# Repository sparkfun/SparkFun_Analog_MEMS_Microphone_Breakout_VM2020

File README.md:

SparkFun Analog MEMS Microphone Breakout - VM2020
========================================

[*SparkFun Analog MEMS Microphone Breakout VM2020 [BOB-21537]*](https://www.sparkfun.com/products/21537)

The SparkFun Analog MEMS Microphone Breakout makes it easy to work with the Vesper VM2020 analog microphone. The VM2020 is an ultra-high Acoustic Overload Point (AOP), high dynamic range, differential analog output piezoelectric MEMS microphone. What separates this from other analog MEMS microphones is that it was designed to be used in loud environments. Additionally, this microphone consists of a piezoelectric sensor and circuitry to buffer and amplify the output. It has an acoustic overload point of 152dB SPL for audio capture in loud environments.

Also note, this low-profile microphone has its port on the bottom side, so the microphone can be mounted flush to the outer surface of your enclosure. This microphone is omnidirectional, which means it does a good job of picking up sound sources from all directions.

Most microphone breakouts in SparkFun's catalog have an OpAmp which amplifies the signal and has a single-ended output. This microphone breakout is differential and does not have an OpAmp. To connect to the differential output with an Arduino, you will need to amplify the signal to a usable level and ADC with differential inputs. We recommend using the SparkFun WM8960 Audio Codec Breakout with a built-in programmable gain amplifier and ADC.

This board is great for applications that require you to measure volume in a loud environment, capture audio when the microphone is next to a speaker, fast Fourier transform analysis of sound at concerts, make your own electronic hearing protection, or create an adaptive filter for your smart speaker. Add the SparkFun VM2020 Analog MEMS Microphone Breakout to your next project!

Repository Contents
-------------------

* **/Documentation** - Data sheets, additional product information
* **/Hardware** - Eagle design files (.brd, .sch)
* **/Hardware/Production** - Production panel files (.brd)

Documentation
--------------
* **[Library](https://github.com/sparkfun/SparkFun_WM8960_Arduino_Library)** - Arduino library for the Stereo Audio Codec Breakout - WM8960 that has an example using a differential microphone (e.g. VM2020).
* **[Fritzing Part](https://github.com/sparkfun/Fritzing_Parts/blob/main/products/21537_sfe_analog_MEMS_microphone_VM2020_differential.fzpz)** - Fritzing diagrams for SparkFun products.
* **[Hookup Guide](https://learn.sparkfun.com/tutorials/2913)** - Basic hookup guide for the SparkFun MEMS microphone breakout.

Product Versions
---------------
* **[BOB-21537](https://www.sparkfun.com/products/21537)** - SparkFun Analog MEMS Microphone Breakout - VM2020

License Information
-------------------

This product is _**open source**_! 

Please review the LICENSE.md file for license information. 

If you have any questions or concerns on licensing, please contact technical support on our [SparkFun forums](https://forum.sparkfun.com/viewforum.php?f=152).

Distributed as-is; no warranty is given.

- Your friends at SparkFun.

_<COLLABORATION CREDIT>_

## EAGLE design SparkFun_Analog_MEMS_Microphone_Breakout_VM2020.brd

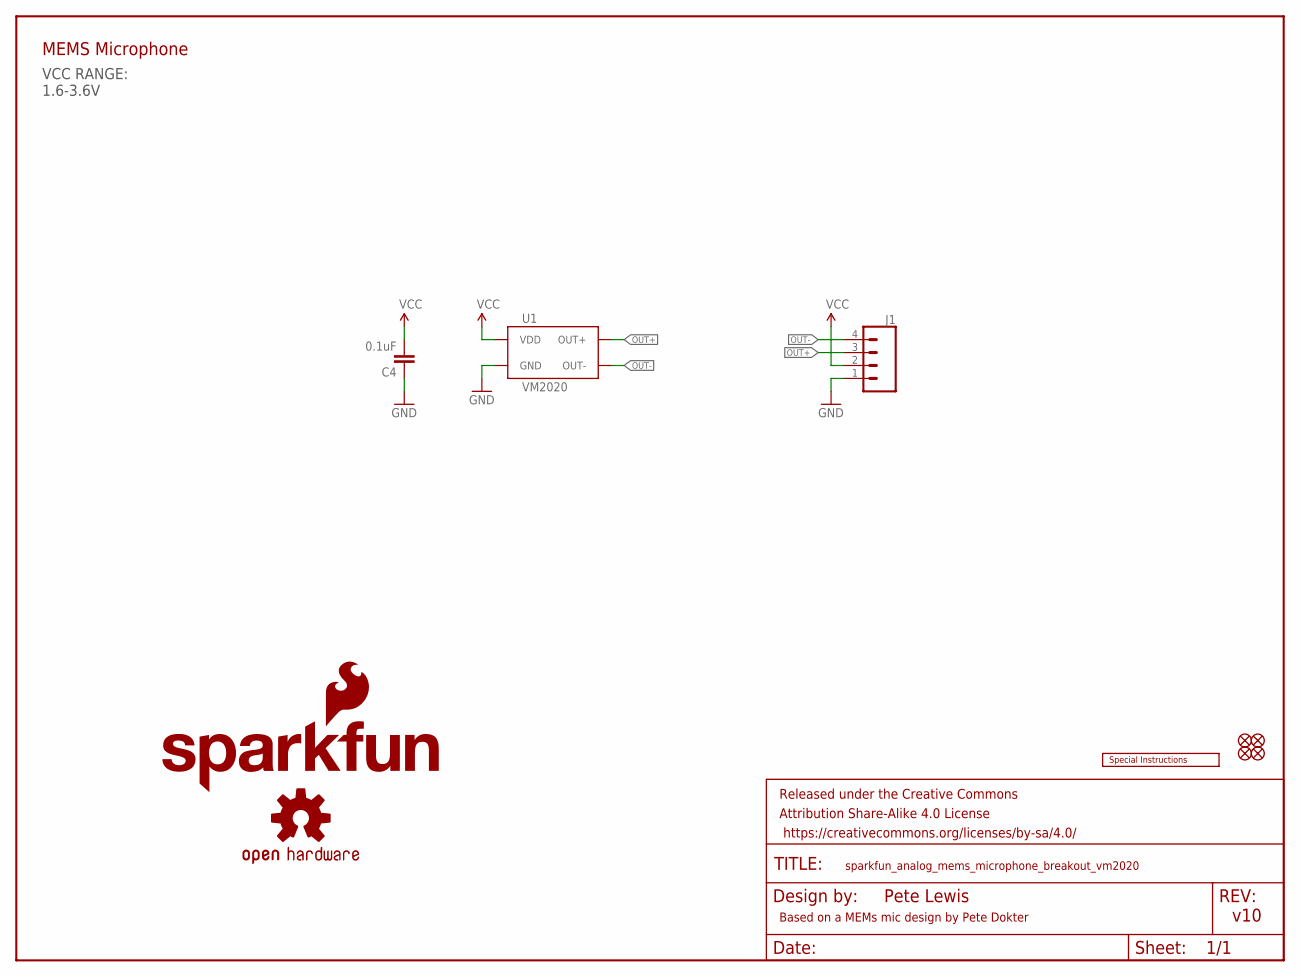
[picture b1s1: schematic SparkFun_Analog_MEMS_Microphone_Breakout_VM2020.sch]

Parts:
C4: 0.1uF; 0603
FD1, FD2, FD3, FD4: FIDUCIALUFIDUCIAL; FIDUCIAL-MICRO
FRAME2: FRAME-LETTER; CREATIVE_COMMONS
J1: CONN_041X04_NO_SILK; 1X04_NO_SILK
LOGO1: SFE_LOGO_FLAME.1_INCH; SFE_LOGO_FLAME_.1
LOGO2: OSHW-LOGOMINI; OSHW-LOGO-MINI
LOGO4: SPECIAL_INSTRUCTIONS-ORDERING; ORDERING_INSTRUCTIONS
U1: VM2020

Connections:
GND: C4.1, J1.1, U1.2 (GND), U1.3 (GND), U1.4 (GND), U1.5 (GND), U1.8 (GND)
OUT+: J1.3, U1.7 (OUT+)
OUT-: J1.4, U1.1 (OUT-)
VCC: C4.2, J1.2, U1.6 (VDD)

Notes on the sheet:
v10
Pete Lewis
VCC RANGE: 1.6-3.6V
MEMS Microphone
Based on a MEMs mic design by Pete Dokter

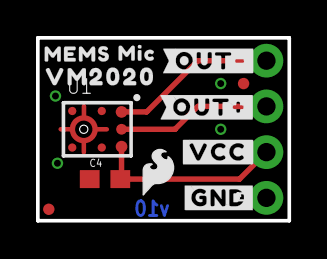
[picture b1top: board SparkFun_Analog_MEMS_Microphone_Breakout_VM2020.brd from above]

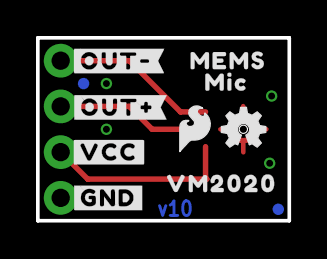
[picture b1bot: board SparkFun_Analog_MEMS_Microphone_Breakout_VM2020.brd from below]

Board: 2 copper layers, 14.0 x 10.2 mm, 26 parts (11 on the bottom side), 4 nets.

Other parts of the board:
LOGO3: SFE_LOGO_FLAME.1_INCH; SFE_LOGO_FLAME_.1
U$3: #OUT##15
U$4: #OUT##18
U$5, U$9: #GND#11
U$6, U$8: VM20200
U$7: MEMS23
U$10, U$11: #VCC#12
U$12: #OUT##19
U$13: #OUT##20
U$14: MEMS21
U$15: MIC22
U$16: MIC24

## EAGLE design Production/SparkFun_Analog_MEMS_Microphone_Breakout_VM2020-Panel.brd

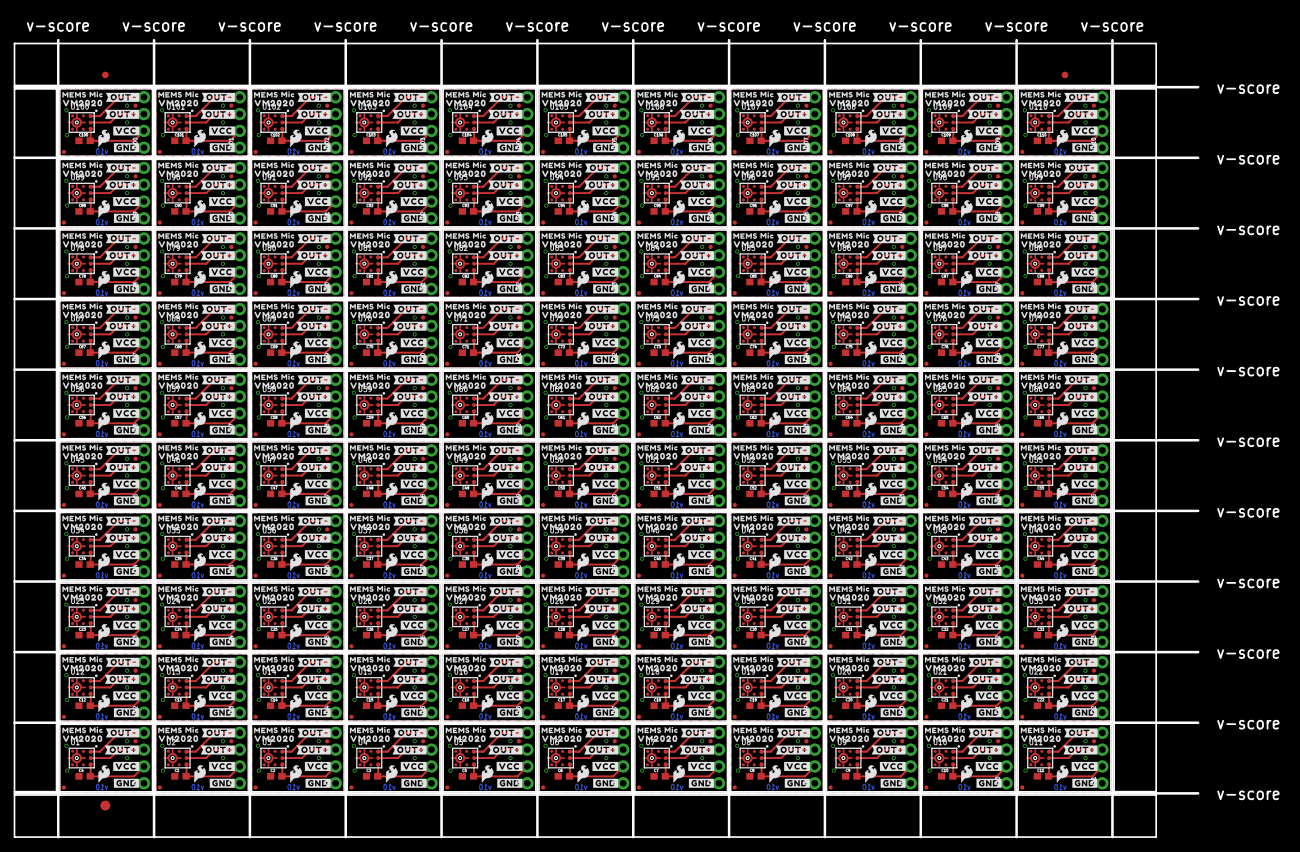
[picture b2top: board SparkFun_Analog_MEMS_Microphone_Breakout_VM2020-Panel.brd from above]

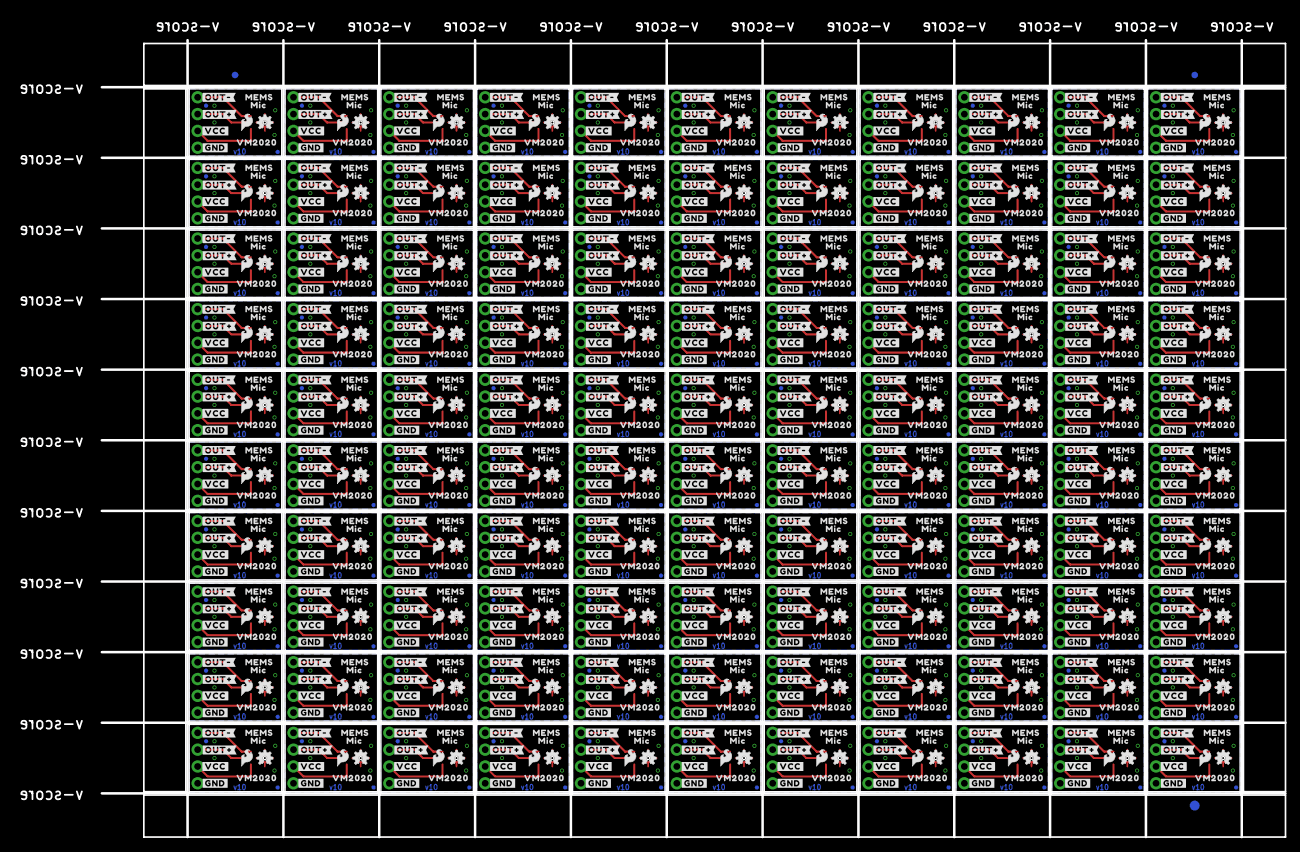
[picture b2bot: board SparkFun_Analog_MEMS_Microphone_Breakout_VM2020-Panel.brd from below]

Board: 2 copper layers, 178.8 x 120.4 mm, 2646 parts (1213 on the bottom side), 440 nets.

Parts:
C1, C2, C3, C4, C5, C6, C7, C8, C9, C10, C11, C12, C13, C14, C15, C16, C17, C18, C19, C20, C21, C22, C23, C24, C25, C26, C27, C28, C29, C30, C31, C32, C33, C34, C35, C36, C37, C38, C39, C40, C41, C42, C43, C44, C45, C46, C47, C48, C49, C50, C51, C52, C53, C54, C55, C56, C57, C58, C59, C60, C61, C62, C63, C64, C65, C66, C67, C68, C69, C70, C71, C72, C73, C74, C75, C76, C77, C78, C79, C80, C81, C82, C83, C84, C85, C86, C87, C88, C89, C90, C91, C92, C93, C94, C95, C96, C97, C98, C99, C100, C101, C102, C103, C104, C105, C106, C107, C108, C109, C110: 0.1uF; 0603
E$1, E$2, E$3, E$4: FIDUCIAL-1X2
E$5, E$6: FIDUCIAL-1.5X3
FD1, FD2, FD3, FD4, FD5, FD6, FD7, FD8, FD9, FD10, FD11, FD12, FD13, FD14, FD15, FD16, FD17, FD18, FD19, FD20, FD21, FD22, FD23, FD24, FD25, FD26, FD27, FD28, FD29, FD30, FD31, FD32, FD33, FD34, FD35, FD36, FD37, FD38, FD39, FD40, FD41, FD42, FD43, FD44, FD45, FD46, FD47, FD48, FD49, FD50, FD51, FD52, FD53, FD54, FD55, FD56, FD57, FD58, FD59, FD60, FD61, FD62, FD63, FD64, FD65, FD66, FD67, FD68, FD69, FD70, FD71, FD72, FD73, FD74, FD75, FD76, FD77, FD78, FD79, FD80, FD81, FD82, FD83, FD84, FD85, FD86, FD87, FD88, FD89, FD90, FD91, FD92, FD93, FD94, FD95, FD96, FD97, FD98, FD99, FD100, FD101, FD102, FD103, FD104, FD105, FD106, FD107, FD108, FD109, FD110, FD111, FD112, FD113, FD114, FD115, FD116, FD117, FD118, FD119, FD120, FD121, FD122, FD123, FD124, FD125, FD126, FD127, FD128, FD129, FD130, FD131, FD132, FD133, FD134, FD135, FD136, FD137, FD138, FD139, FD140, FD141, FD142, FD143, FD144, FD145, FD146, FD147, FD148, FD149, FD150, FD151, FD152, FD153, FD154, FD155, FD156, FD157, FD158, FD159, FD160, FD161, FD162, FD163, FD164, FD165, FD166, FD167, FD168, FD169, FD170, FD171, FD172, FD173, FD174, FD175, FD176, FD177, FD178, FD179, FD180, FD181, FD182, FD183, FD184, FD185, FD186, FD187, FD188, FD189, FD190, FD191, FD192, FD193, FD194, FD195, FD196, FD197, FD198, FD199, FD200, FD201, FD202, FD203, FD204, FD205, FD206, FD207, FD208, FD209, FD210, FD211, FD212, FD213, FD214, FD215, FD216, FD217, FD218, FD219, FD220, FD221, FD222, FD223, FD224, FD225, FD226, FD227, FD228, FD229, FD230, FD231, FD232, FD233, FD234, FD235, FD236, FD237, FD238, FD239, FD240, FD241, FD242, FD243, FD244, FD245, FD246, FD247, FD248, FD249, FD250, FD251, FD252, FD253, FD254, FD255, FD256, FD257, FD258, FD259, FD260, FD261, FD262, FD263, FD264, FD265, FD266, FD267, FD268, FD269, FD270, FD271, FD272, FD273, FD274, FD275, FD276, FD277, FD278, FD279, FD280, FD281, FD282, FD283, FD284, FD285, FD286, FD287, FD288, FD289, FD290, FD291, FD292, FD293, FD294, FD295, FD296, FD297, FD298, FD299, FD300, FD301, FD302, FD303, FD304, FD305, FD306, FD307, FD308, FD309, FD310, FD311, FD312, FD313, FD314, FD315, FD316, FD317, FD318, FD319, FD320, FD321, FD322, FD323, FD324, FD325, FD326, FD327, FD328, FD329, FD330, FD331, FD332, FD333, FD334, FD335, FD336, FD337, FD338, FD339, FD340, FD341, FD342, FD343, FD344, FD345, FD346, FD347, FD348, FD349, FD350, FD351, FD352, FD353, FD354, FD355, FD356, FD357, FD358, FD359, FD360, FD361, FD362, FD363, FD364, FD365, FD366, FD367, FD368, FD369, FD370, FD371, FD372, FD373, FD374, FD375, FD376, FD377, FD378, FD379, FD380, FD381, FD382, FD383, FD384, FD385, FD386, FD387, FD388, FD389, FD390, FD391, FD392, FD393, FD394, FD395, FD396, FD397, FD398, FD399, FD400, FD401, FD402, FD403, FD404, FD405, FD406, FD407, FD408, FD409, FD410, FD411, FD412, FD413, FD414, FD415, FD416, FD417, FD418, FD419, FD420, FD421, FD422, FD423, FD424, FD425, FD426, FD427, FD428, FD429, FD430, FD431, FD432, FD433, FD434, FD435, FD436, FD437, FD438, FD439, FD440: FIDUCIALUFIDUCIAL; FIDUCIAL-MICRO
J1, J2, J3, J4, J5, J6, J7, J8, J9, J10, J11, J12, J13, J14, J15, J16, J17, J18, J19, J20, J21, J22, J23, J24, J25, J26, J27, J28, J29, J30, J31, J32, J33, J34, J35, J36, J37, J38, J39, J40, J41, J42, J43, J44, J45, J46, J47, J48, J49, J50, J51, J52, J53, J54, J55, J56, J57, J58, J59, J60, J61, J62, J63, J64, J65, J66, J67, J68, J69, J70, J71, J72, J73, J74, J75, J76, J77, J78, J79, J80, J81, J82, J83, J84, J85, J86, J87, J88, J89, J90, J91, J92, J93, J94, J95, J96, J97, J98, J99, J100, J101, J102, J103, J104, J105, J106, J107, J108, J109, J110: 1X04_NO_SILK
LOGO1, LOGO3, LOGO4, LOGO6, LOGO7, LOGO9, LOGO10, LOGO12, LOGO13, LOGO15, LOGO16, LOGO18, LOGO19, LOGO21, LOGO22, LOGO24, LOGO25, LOGO27, LOGO28, LOGO30, LOGO31, LOGO33, LOGO34, LOGO36, LOGO37, LOGO39, LOGO40, LOGO42, LOGO43, LOGO45, LOGO46, LOGO48, LOGO49, LOGO51, LOGO52, LOGO54, LOGO55, LOGO57, LOGO58, LOGO60, LOGO61, LOGO63, LOGO64, LOGO66, LOGO67, LOGO69, LOGO70, LOGO72, LOGO73, LOGO75, LOGO76, LOGO78, LOGO79, LOGO81, LOGO82, LOGO84, LOGO85, LOGO87, LOGO88, LOGO90, LOGO91, LOGO93, LOGO94, LOGO96, LOGO97, LOGO99, LOGO100, LOGO102, LOGO103, LOGO105, LOGO106, LOGO108, LOGO109, LOGO111, LOGO112, LOGO114, LOGO115, LOGO117, LOGO118, LOGO120, LOGO121, LOGO123, LOGO124, LOGO126, LOGO127, LOGO129, LOGO130, LOGO132, LOGO133, LOGO135, LOGO136, LOGO138, LOGO139, LOGO141, LOGO142, LOGO144, LOGO145, LOGO147, LOGO148, LOGO150, LOGO151, LOGO153, LOGO154, LOGO156, LOGO157, LOGO159, LOGO160, LOGO162, LOGO163, LOGO165, LOGO166, LOGO168, LOGO169, LOGO171, LOGO172, LOGO174, LOGO175, LOGO177, LOGO178, LOGO180, LOGO181, LOGO183, LOGO184, LOGO186, LOGO187, LOGO189, LOGO190, LOGO192, LOGO193, LOGO195, LOGO196, LOGO198, LOGO199, LOGO201, LOGO202, LOGO204, LOGO205, LOGO207, LOGO208, LOGO210, LOGO211, LOGO213, LOGO214, LOGO216, LOGO217, LOGO219, LOGO220, LOGO222, LOGO223, LOGO225, LOGO226, LOGO228, LOGO229, LOGO231, LOGO232, LOGO234, LOGO235, LOGO237, LOGO238, LOGO240, LOGO241, LOGO243, LOGO244, LOGO246, LOGO247, LOGO249, LOGO250, LOGO252, LOGO253, LOGO255, LOGO256, LOGO258, LOGO259, LOGO261, LOGO262, LOGO264, LOGO265, LOGO267, LOGO268, LOGO270, LOGO271, LOGO273, LOGO274, LOGO276, LOGO277, LOGO279, LOGO280, LOGO282, LOGO283, LOGO285, LOGO286, LOGO288, LOGO289, LOGO291, LOGO292, LOGO294, LOGO295, LOGO297, LOGO298, LOGO300, LOGO301, LOGO303, LOGO304, LOGO306, LOGO307, LOGO309, LOGO310, LOGO312, LOGO313, LOGO315, LOGO316, LOGO318, LOGO319, LOGO321, LOGO322, LOGO324, LOGO325, LOGO327, LOGO328, LOGO330: SFE_LOGO_FLAME.1_INCH; SFE_LOGO_FLAME_.1
LOGO2, LOGO5, LOGO8, LOGO11, LOGO14, LOGO17, LOGO20, LOGO23, LOGO26, LOGO29, LOGO32, LOGO35, LOGO38, LOGO41, LOGO44, LOGO47, LOGO50, LOGO53, LOGO56, LOGO59, LOGO62, LOGO65, LOGO68, LOGO71, LOGO74, LOGO77, LOGO80, LOGO83, LOGO86, LOGO89, LOGO92, LOGO95, LOGO98, LOGO101, LOGO104, LOGO107, LOGO110, LOGO113, LOGO116, LOGO119, LOGO122, LOGO125, LOGO128, LOGO131, LOGO134, LOGO137, LOGO140, LOGO143, LOGO146, LOGO149, LOGO152, LOGO155, LOGO158, LOGO161, LOGO164, LOGO167, LOGO170, LOGO173, LOGO176, LOGO179, LOGO182, LOGO185, LOGO188, LOGO191, LOGO194, LOGO197, LOGO200, LOGO203, LOGO206, LOGO209, LOGO212, LOGO215, LOGO218, LOGO221, LOGO224, LOGO227, LOGO230, LOGO233, LOGO236, LOGO239, LOGO242, LOGO245, LOGO248, LOGO251, LOGO254, LOGO257, LOGO260, LOGO263, LOGO266, LOGO269, LOGO272, LOGO275, LOGO278, LOGO281, LOGO284, LOGO287, LOGO290, LOGO293, LOGO296, LOGO299, LOGO302, LOGO305, LOGO308, LOGO311, LOGO314, LOGO317, LOGO320, LOGO323, LOGO326, LOGO329: OSHW-LOGOMINI; OSHW-LOGO-MINI
U1, U2, U3, U4, U5, U6, U7, U8, U9, U10, U11, U12, U13, U14, U15, U16, U17, U18, U19, U20, U21, U22, U23, U24, U25, U26, U27, U28, U29, U30, U31, U32, U33, U34, U35, U36, U37, U38, U39, U40, U41, U42, U43, U44, U45, U46, U47, U48, U49, U50, U51, U52, U53, U54, U55, U56, U57, U58, U59, U60, U61, U62, U63, U64, U65, U66, U67, U68, U69, U70, U71, U72, U73, U74, U75, U76, U77, U78, U79, U80, U81, U82, U83, U84, U85, U86, U87, U88, U89, U90, U91, U92, U93, U94, U95, U96, U97, U98, U99, U100, U101, U102, U103, U104, U105, U106, U107, U108, U109, U110: VM2020
U$1, U$2, U$6, U$8, U$29, U$30, U$43, U$44, U$57, U$58, U$71, U$72, U$85, U$86, U$99, U$100, U$113, U$114, U$127, U$128, U$141, U$142, U$155, U$156, U$169, U$170, U$183, U$184, U$197, U$198, U$211, U$212, U$225, U$226, U$239, U$240, U$253, U$254, U$267, U$268, U$281, U$282, U$295, U$296, U$309, U$310, U$323, U$324, U$337, U$338, U$351, U$352, U$365, U$366, U$379, U$380, U$393, U$394, U$407, U$408, U$421, U$422, U$435, U$436, U$449, U$450, U$463, U$464, U$477, U$478, U$491, U$492, U$505, U$506, U$519, U$520, U$533, U$534, U$547, U$548, U$561, U$562, U$575, U$576, U$589, U$590, U$603, U$604, U$617, U$618, U$631, U$632, U$645, U$646, U$659, U$660, U$673, U$674, U$687, U$688, U$701, U$702, U$715, U$716, U$729, U$730, U$743, U$744, U$757, U$758, U$771, U$772, U$785, U$786, U$799, U$800, U$813, U$814, U$827, U$828, U$841, U$842, U$855, U$856, U$869, U$870, U$883, U$884, U$897, U$898, U$911, U$912, U$925, U$926, U$939, U$940, U$953, U$954, U$967, U$968, U$981, U$982, U$995, U$996, U$1009, U$1010, U$1023, U$1024, U$1037, U$1038, U$1051, U$1052, U$1065, U$1066, U$1079, U$1080, U$1093, U$1094, U$1107, U$1108, U$1121, U$1122, U$1135, U$1136, U$1149, U$1150, U$1163, U$1164, U$1177, U$1178, U$1191, U$1192, U$1205, U$1206, U$1219, U$1220, U$1233, U$1234, U$1247, U$1248, U$1261, U$1262, U$1275, U$1276, U$1289, U$1290, U$1303, U$1304, U$1317, U$1318, U$1331, U$1332, U$1345, U$1346, U$1359, U$1360, U$1373, U$1374, U$1387, U$1388, U$1401, U$1402, U$1415, U$1416, U$1429, U$1430, U$1443, U$1444, U$1457, U$1458, U$1471, U$1472, U$1485, U$1486, U$1499, U$1500, U$1513, U$1514, U$1527, U$1528: VM20200
U$3, U$21, U$35, U$49, U$63, U$77, U$91, U$105, U$119, U$133, U$147, U$161, U$175, U$189, U$203, U$217, U$231, U$245, U$259, U$273, U$287, U$301, U$315, U$329, U$343, U$357, U$371, U$385, U$399, U$413, U$427, U$441, U$455, U$469, U$483, U$497, U$511, U$525, U$539, U$553, U$567, U$581, U$595, U$609, U$623, U$637, U$651, U$665, U$679, U$693, U$707, U$721, U$735, U$749, U$763, U$777, U$791, U$805, U$819, U$833, U$847, U$861, U$875, U$889, U$903, U$917, U$931, U$945, U$959, U$973, U$987, U$1001, U$1015, U$1029, U$1043, U$1057, U$1071, U$1085, U$1099, U$1113, U$1127, U$1141, U$1155, U$1169, U$1183, U$1197, U$1211, U$1225, U$1239, U$1253, U$1267, U$1281, U$1295, U$1309, U$1323, U$1337, U$1351, U$1365, U$1379, U$1393, U$1407, U$1421, U$1435, U$1449, U$1463, U$1477, U$1491, U$1505, U$1519, U$1533: #OUT##15
U$4, U$22, U$36, U$50, U$64, U$78, U$92, U$106, U$120, U$134, U$148, U$162, U$176, U$190, U$204, U$218, U$232, U$246, U$260, U$274, U$288, U$302, U$316, U$330, U$344, U$358, U$372, U$386, U$400, U$414, U$428, U$442, U$456, U$470, U$484, U$498, U$512, U$526, U$540, U$554, U$568, U$582, U$596, U$610, U$624, U$638, U$652, U$666, U$680, U$694, U$708, U$722, U$736, U$750, U$764, U$778, U$792, U$806, U$820, U$834, U$848, U$862, U$876, U$890, U$904, U$918, U$932, U$946, U$960, U$974, U$988, U$1002, U$1016, U$1030, U$1044, U$1058, U$1072, U$1086, U$1100, U$1114, U$1128, U$1142, U$1156, U$1170, U$1184, U$1198, U$1212, U$1226, U$1240, U$1254, U$1268, U$1282, U$1296, U$1310, U$1324, U$1338, U$1352, U$1366, U$1380, U$1394, U$1408, U$1422, U$1436, U$1450, U$1464, U$1478, U$1492, U$1506, U$1520, U$1534: #OUT##18
U$5, U$9, U$17, U$18, U$31, U$32, U$45, U$46, U$59, U$60, U$73, U$74, U$87, U$88, U$101, U$102, U$115, U$116, U$129, U$130, U$143, U$144, U$157, U$158, U$171, U$172, U$185, U$186, U$199, U$200, U$213, U$214, U$227, U$228, U$241, U$242, U$255, U$256, U$269, U$270, U$283, U$284, U$297, U$298, U$311, U$312, U$325, U$326, U$339, U$340, U$353, U$354, U$367, U$368, U$381, U$382, U$395, U$396, U$409, U$410, U$423, U$424, U$437, U$438, U$451, U$452, U$465, U$466, U$479, U$480, U$493, U$494, U$507, U$508, U$521, U$522, U$535, U$536, U$549, U$550, U$563, U$564, U$577, U$578, U$591, U$592, U$605, U$606, U$619, U$620, U$633, U$634, U$647, U$648, U$661, U$662, U$675, U$676, U$689, U$690, U$703, U$704, U$717, U$718, U$731, U$732, U$745, U$746, U$759, U$760, U$773, U$774, U$787, U$788, U$801, U$802, U$815, U$816, U$829, U$830, U$843, U$844, U$857, U$858, U$871, U$872, U$885, U$886, U$899, U$900, U$913, U$914, U$927, U$928, U$941, U$942, U$955, U$956, U$969, U$970, U$983, U$984, U$997, U$998, U$1011, U$1012, U$1025, U$1026, U$1039, U$1040, U$1053, U$1054, U$1067, U$1068, U$1081, U$1082, U$1095, U$1096, U$1109, U$1110, U$1123, U$1124, U$1137, U$1138, U$1151, U$1152, U$1165, U$1166, U$1179, U$1180, U$1193, U$1194, U$1207, U$1208, U$1221, U$1222, U$1235, U$1236, U$1249, U$1250, U$1263, U$1264, U$1277, U$1278, U$1291, U$1292, U$1305, U$1306, U$1319, U$1320, U$1333, U$1334, U$1347, U$1348, U$1361, U$1362, U$1375, U$1376, U$1389, U$1390, U$1403, U$1404, U$1417, U$1418, U$1431, U$1432, U$1445, U$1446, U$1459, U$1460, U$1473, U$1474, U$1487, U$1488, U$1501, U$1502, U$1515, U$1516, U$1529, U$1530: #GND#11
U$7, U$27, U$41, U$55, U$69, U$83, U$97, U$111, U$125, U$139, U$153, U$167, U$181, U$195, U$209, U$223, U$237, U$251, U$265, U$279, U$293, U$307, U$321, U$335, U$349, U$363, U$377, U$391, U$405, U$419, U$433, U$447, U$461, U$475, U$489, U$503, U$517, U$531, U$545, U$559, U$573, U$587, U$601, U$615, U$629, U$643, U$657, U$671, U$685, U$699, U$713, U$727, U$741, U$755, U$769, U$783, U$797, U$811, U$825, U$839, U$853, U$867, U$881, U$895, U$909, U$923, U$937, U$951, U$965, U$979, U$993, U$1007, U$1021, U$1035, U$1049, U$1063, U$1077, U$1091, U$1105, U$1119, U$1133, U$1147, U$1161, U$1175, U$1189, U$1203, U$1217, U$1231, U$1245, U$1259, U$1273, U$1287, U$1301, U$1315, U$1329, U$1343, U$1357, U$1371, U$1385, U$1399, U$1413, U$1427, U$1441, U$1455, U$1469, U$1483, U$1497, U$1511, U$1525, U$1539: MEMS23
U$10, U$11, U$19, U$20, U$33, U$34, U$47, U$48, U$61, U$62, U$75, U$76, U$89, U$90, U$103, U$104, U$117, U$118, U$131, U$132, U$145, U$146, U$159, U$160, U$173, U$174, U$187, U$188, U$201, U$202, U$215, U$216, U$229, U$230, U$243, U$244, U$257, U$258, U$271, U$272, U$285, U$286, U$299, U$300, U$313, U$314, U$327, U$328, U$341, U$342, U$355, U$356, U$369, U$370, U$383, U$384, U$397, U$398, U$411, U$412, U$425, U$426, U$439, U$440, U$453, U$454, U$467, U$468, U$481, U$482, U$495, U$496, U$509, U$510, U$523, U$524, U$537, U$538, U$551, U$552, U$565, U$566, U$579, U$580, U$593, U$594, U$607, U$608, U$621, U$622, U$635, U$636, U$649, U$650, U$663, U$664, U$677, U$678, U$691, U$692, U$705, U$706, U$719, U$720, U$733, U$734, U$747, U$748, U$761, U$762, U$775, U$776, U$789, U$790, U$803, U$804, U$817, U$818, U$831, U$832, U$845, U$846, U$859, U$860, U$873, U$874, U$887, U$888, U$901, U$902, U$915, U$916, U$929, U$930, U$943, U$944, U$957, U$958, U$971, U$972, U$985, U$986, U$999, U$1000, U$1013, U$1014, U$1027, U$1028, U$1041, U$1042, U$1055, U$1056, U$1069, U$1070, U$1083, U$1084, U$1097, U$1098, U$1111, U$1112, U$1125, U$1126, U$1139, U$1140, U$1153, U$1154, U$1167, U$1168, U$1181, U$1182, U$1195, U$1196, U$1209, U$1210, U$1223, U$1224, U$1237, U$1238, U$1251, U$1252, U$1265, U$1266, U$1279, U$1280, U$1293, U$1294, U$1307, U$1308, U$1321, U$1322, U$1335, U$1336, U$1349, U$1350, U$1363, U$1364, U$1377, U$1378, U$1391, U$1392, U$1405, U$1406, U$1419, U$1420, U$1433, U$1434, U$1447, U$1448, U$1461, U$1462, U$1475, U$1476, U$1489, U$1490, U$1503, U$1504, U$1517, U$1518, U$1531, U$1532: #VCC#12
U$12, U$23, U$37, U$51, U$65, U$79, U$93, U$107, U$121, U$135, U$149, U$163, U$177, U$191, U$205, U$219, U$233, U$247, U$261, U$275, U$289, U$303, U$317, U$331, U$345, U$359, U$373, U$387, U$401, U$415, U$429, U$443, U$457, U$471, U$485, U$499, U$513, U$527, U$541, U$555, U$569, U$583, U$597, U$611, U$625, U$639, U$653, U$667, U$681, U$695, U$709, U$723, U$737, U$751, U$765, U$779, U$793, U$807, U$821, U$835, U$849, U$863, U$877, U$891, U$905, U$919, U$933, U$947, U$961, U$975, U$989, U$1003, U$1017, U$1031, U$1045, U$1059, U$1073, U$1087, U$1101, U$1115, U$1129, U$1143, U$1157, U$1171, U$1185, U$1199, U$1213, U$1227, U$1241, U$1255, U$1269, U$1283, U$1297, U$1311, U$1325, U$1339, U$1353, U$1367, U$1381, U$1395, U$1409, U$1423, U$1437, U$1451, U$1465, U$1479, U$1493, U$1507, U$1521, U$1535: #OUT##19
U$13, U$24, U$38, U$52, U$66, U$80, U$94, U$108, U$122, U$136, U$150, U$164, U$178, U$192, U$206, U$220, U$234, U$248, U$262, U$276, U$290, U$304, U$318, U$332, U$346, U$360, U$374, U$388, U$402, U$416, U$430, U$444, U$458, U$472, U$486, U$500, U$514, U$528, U$542, U$556, U$570, U$584, U$598, U$612, U$626, U$640, U$654, U$668, U$682, U$696, U$710, U$724, U$738, U$752, U$766, U$780, U$794, U$808, U$822, U$836, U$850, U$864, U$878, U$892, U$906, U$920, U$934, U$948, U$962, U$976, U$990, U$1004, U$1018, U$1032, U$1046, U$1060, U$1074, U$1088, U$1102, U$1116, U$1130, U$1144, U$1158, U$1172, U$1186, U$1200, U$1214, U$1228, U$1242, U$1256, U$1270, U$1284, U$1298, U$1312, U$1326, U$1340, U$1354, U$1368, U$1382, U$1396, U$1410, U$1424, U$1438, U$1452, U$1466, U$1480, U$1494, U$1508, U$1522, U$1536: #OUT##20
U$14, U$25, U$39, U$53, U$67, U$81, U$95, U$109, U$123, U$137, U$151, U$165, U$179, U$193, U$207, U$221, U$235, U$249, U$263, U$277, U$291, U$305, U$319, U$333, U$347, U$361, U$375, U$389, U$403, U$417, U$431, U$445, U$459, U$473, U$487, U$501, U$515, U$529, U$543, U$557, U$571, U$585, U$599, U$613, U$627, U$641, U$655, U$669, U$683, U$697, U$711, U$725, U$739, U$753, U$767, U$781, U$795, U$809, U$823, U$837, U$851, U$865, U$879, U$893, U$907, U$921, U$935, U$949, U$963, U$977, U$991, U$1005, U$1019, U$1033, U$1047, U$1061, U$1075, U$1089, U$1103, U$1117, U$1131, U$1145, U$1159, U$1173, U$1187, U$1201, U$1215, U$1229, U$1243, U$1257, U$1271, U$1285, U$1299, U$1313, U$1327, U$1341, U$1355, U$1369, U$1383, U$1397, U$1411, U$1425, U$1439, U$1453, U$1467, U$1481, U$1495, U$1509, U$1523, U$1537: MEMS21
U$15, U$26, U$40, U$54, U$68, U$82, U$96, U$110, U$124, U$138, U$152, U$166, U$180, U$194, U$208, U$222, U$236, U$250, U$264, U$278, U$292, U$306, U$320, U$334, U$348, U$362, U$376, U$390, U$404, U$418, U$432, U$446, U$460, U$474, U$488, U$502, U$516, U$530, U$544, U$558, U$572, U$586, U$600, U$614, U$628, U$642, U$656, U$670, U$684, U$698, U$712, U$726, U$740, U$754, U$768, U$782, U$796, U$810, U$824, U$838, U$852, U$866, U$880, U$894, U$908, U$922, U$936, U$950, U$964, U$978, U$992, U$1006, U$1020, U$1034, U$1048, U$1062, U$1076, U$1090, U$1104, U$1118, U$1132, U$1146, U$1160, U$1174, U$1188, U$1202, U$1216, U$1230, U$1244, U$1258, U$1272, U$1286, U$1300, U$1314, U$1328, U$1342, U$1356, U$1370, U$1384, U$1398, U$1412, U$1426, U$1440, U$1454, U$1468, U$1482, U$1496, U$1510, U$1524, U$1538: MIC22
U$16, U$28, U$42, U$56, U$70, U$84, U$98, U$112, U$126, U$140, U$154, U$168, U$182, U$196, U$210, U$224, U$238, U$252, U$266, U$280, U$294, U$308, U$322, U$336, U$350, U$364, U$378, U$392, U$406, U$420, U$434, U$448, U$462, U$476, U$490, U$504, U$518, U$532, U$546, U$560, U$574, U$588, U$602, U$616, U$630, U$644, U$658, U$672, U$686, U$700, U$714, U$728, U$742, U$756, U$770, U$784, U$798, U$812, U$826, U$840, U$854, U$868, U$882, U$896, U$910, U$924, U$938, U$952, U$966, U$980, U$994, U$1008, U$1022, U$1036, U$1050, U$1064, U$1078, U$1092, U$1106, U$1120, U$1134, U$1148, U$1162, U$1176, U$1190, U$1204, U$1218, U$1232, U$1246, U$1260, U$1274, U$1288, U$1302, U$1316, U$1330, U$1344, U$1358, U$1372, U$1386, U$1400, U$1414, U$1428, U$1442, U$1456, U$1470, U$1484, U$1498, U$1512, U$1526, U$1540: MIC24

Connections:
GND: C4.1, J1.1, U1.2, U1.3, U1.4, U1.5, U1.8
GND1: C1.1, J2.1, U2.2, U2.3, U2.4, U2.5, U2.8
GND2: C2.1, J3.1, U3.2, U3.3, U3.4, U3.5, U3.8
GND3: C3.1, J4.1, U4.2, U4.3, U4.4, U4.5, U4.8
GND4: C5.1, J5.1, U5.2, U5.3, U5.4, U5.5, U5.8
GND5: C6.1, J6.1, U6.2, U6.3, U6.4, U6.5, U6.8
GND6: C7.1, J7.1, U7.2, U7.3, U7.4, U7.5, U7.8
GND7: C8.1, J8.1, U8.2, U8.3, U8.4, U8.5, U8.8
GND8: C9.1, J9.1, U9.2, U9.3, U9.4, U9.5, U9.8
GND9: C10.1, J10.1, U10.2, U10.3, U10.4, U10.5, U10.8
GND10: C11.1, J11.1, U11.2, U11.3, U11.4, U11.5, U11.8
GND11: C12.1, J12.1, U12.2, U12.3, U12.4, U12.5, U12.8
GND12: C13.1, J13.1, U13.2, U13.3, U13.4, U13.5, U13.8
GND13: C14.1, J14.1, U14.2, U14.3, U14.4, U14.5, U14.8
GND14: C15.1, J15.1, U15.2, U15.3, U15.4, U15.5, U15.8
GND15: C16.1, J16.1, U16.2, U16.3, U16.4, U16.5, U16.8
GND16: C17.1, J17.1, U17.2, U17.3, U17.4, U17.5, U17.8
GND17: C18.1, J18.1, U18.2, U18.3, U18.4, U18.5, U18.8
GND18: C19.1, J19.1, U19.2, U19.3, U19.4, U19.5, U19.8
GND19: C20.1, J20.1, U20.2, U20.3, U20.4, U20.5, U20.8
GND20: C21.1, J21.1, U21.2, U21.3, U21.4, U21.5, U21.8
GND21: C22.1, J22.1, U22.2, U22.3, U22.4, U22.5, U22.8
GND22: C23.1, J23.1, U23.2, U23.3, U23.4, U23.5, U23.8
GND23: C24.1, J24.1, U24.2, U24.3, U24.4, U24.5, U24.8
GND24: C25.1, J25.1, U25.2, U25.3, U25.4, U25.5, U25.8
GND25: C26.1, J26.1, U26.2, U26.3, U26.4, U26.5, U26.8
GND26: C27.1, J27.1, U27.2, U27.3, U27.4, U27.5, U27.8
GND27: C28.1, J28.1, U28.2, U28.3, U28.4, U28.5, U28.8
GND28: C29.1, J29.1, U29.2, U29.3, U29.4, U29.5, U29.8
GND29: C30.1, J30.1, U30.2, U30.3, U30.4, U30.5, U30.8
GND30: C31.1, J31.1, U31.2, U31.3, U31.4, U31.5, U31.8
GND31: C32.1, J32.1, U32.2, U32.3, U32.4, U32.5, U32.8
GND32: C33.1, J33.1, U33.2, U33.3, U33.4, U33.5, U33.8
GND33: C34.1, J34.1, U34.2, U34.3, U34.4, U34.5, U34.8
GND34: C35.1, J35.1, U35.2, U35.3, U35.4, U35.5, U35.8
GND35: C36.1, J36.1, U36.2, U36.3, U36.4, U36.5, U36.8
GND36: C37.1, J37.1, U37.2, U37.3, U37.4, U37.5, U37.8
GND37: C38.1, J38.1, U38.2, U38.3, U38.4, U38.5, U38.8
GND38: C39.1, J39.1, U39.2, U39.3, U39.4, U39.5, U39.8
GND39: C40.1, J40.1, U40.2, U40.3, U40.4, U40.5, U40.8
GND40: C41.1, J41.1, U41.2, U41.3, U41.4, U41.5, U41.8
GND41: C42.1, J42.1, U42.2, U42.3, U42.4, U42.5, U42.8
GND42: C43.1, J43.1, U43.2, U43.3, U43.4, U43.5, U43.8
GND43: C44.1, J44.1, U44.2, U44.3, U44.4, U44.5, U44.8
GND44: C45.1, J45.1, U45.2, U45.3, U45.4, U45.5, U45.8
GND45: C46.1, J46.1, U46.2, U46.3, U46.4, U46.5, U46.8
GND46: C47.1, J47.1, U47.2, U47.3, U47.4, U47.5, U47.8
GND47: C48.1, J48.1, U48.2, U48.3, U48.4, U48.5, U48.8
GND48: C49.1, J49.1, U49.2, U49.3, U49.4, U49.5, U49.8
GND49: C50.1, J50.1, U50.2, U50.3, U50.4, U50.5, U50.8
GND50: C51.1, J51.1, U51.2, U51.3, U51.4, U51.5, U51.8
GND51: C52.1, J52.1, U52.2, U52.3, U52.4, U52.5, U52.8
GND52: C53.1, J53.1, U53.2, U53.3, U53.4, U53.5, U53.8
GND53: C54.1, J54.1, U54.2, U54.3, U54.4, U54.5, U54.8
GND54: C55.1, J55.1, U55.2, U55.3, U55.4, U55.5, U55.8
GND55: C56.1, J56.1, U56.2, U56.3, U56.4, U56.5, U56.8
GND56: C57.1, J57.1, U57.2, U57.3, U57.4, U57.5, U57.8
GND57: C58.1, J58.1, U58.2, U58.3, U58.4, U58.5, U58.8
GND58: C59.1, J59.1, U59.2, U59.3, U59.4, U59.5, U59.8
GND59: C60.1, J60.1, U60.2, U60.3, U60.4, U60.5, U60.8
GND60: C61.1, J61.1, U61.2, U61.3, U61.4, U61.5, U61.8
GND61: C62.1, J62.1, U62.2, U62.3, U62.4, U62.5, U62.8
GND62: C63.1, J63.1, U63.2, U63.3, U63.4, U63.5, U63.8
GND63: C64.1, J64.1, U64.2, U64.3, U64.4, U64.5, U64.8
GND64: C65.1, J65.1, U65.2, U65.3, U65.4, U65.5, U65.8
GND65: C66.1, J66.1, U66.2, U66.3, U66.4, U66.5, U66.8
GND66: C67.1, J67.1, U67.2, U67.3, U67.4, U67.5, U67.8
GND67: C68.1, J68.1, U68.2, U68.3, U68.4, U68.5, U68.8
GND68: C69.1, J69.1, U69.2, U69.3, U69.4, U69.5, U69.8
GND69: C70.1, J70.1, U70.2, U70.3, U70.4, U70.5, U70.8
GND70: C71.1, J71.1, U71.2, U71.3, U71.4, U71.5, U71.8
GND71: C72.1, J72.1, U72.2, U72.3, U72.4, U72.5, U72.8
GND72: C73.1, J73.1, U73.2, U73.3, U73.4, U73.5, U73.8
GND73: C74.1, J74.1, U74.2, U74.3, U74.4, U74.5, U74.8
GND74: C75.1, J75.1, U75.2, U75.3, U75.4, U75.5, U75.8
GND75: C76.1, J76.1, U76.2, U76.3, U76.4, U76.5, U76.8
GND76: C77.1, J77.1, U77.2, U77.3, U77.4, U77.5, U77.8
GND77: C78.1, J78.1, U78.2, U78.3, U78.4, U78.5, U78.8
GND78: C79.1, J79.1, U79.2, U79.3, U79.4, U79.5, U79.8
GND79: C80.1, J80.1, U80.2, U80.3, U80.4, U80.5, U80.8
GND80: C81.1, J81.1, U81.2, U81.3, U81.4, U81.5, U81.8
GND81: C82.1, J82.1, U82.2, U82.3, U82.4, U82.5, U82.8
GND82: C83.1, J83.1, U83.2, U83.3, U83.4, U83.5, U83.8
GND83: C84.1, J84.1, U84.2, U84.3, U84.4, U84.5, U84.8
GND84: C85.1, J85.1, U85.2, U85.3, U85.4, U85.5, U85.8
GND85: C86.1, J86.1, U86.2, U86.3, U86.4, U86.5, U86.8
GND86: C87.1, J87.1, U87.2, U87.3, U87.4, U87.5, U87.8
GND87: C88.1, J88.1, U88.2, U88.3, U88.4, U88.5, U88.8
GND88: C89.1, J89.1, U89.2, U89.3, U89.4, U89.5, U89.8
GND89: C90.1, J90.1, U90.2, U90.3, U90.4, U90.5, U90.8
GND90: C91.1, J91.1, U91.2, U91.3, U91.4, U91.5, U91.8
GND91: C92.1, J92.1, U92.2, U92.3, U92.4, U92.5, U92.8
GND92: C93.1, J93.1, U93.2, U93.3, U93.4, U93.5, U93.8
GND93: C94.1, J94.1, U94.2, U94.3, U94.4, U94.5, U94.8
GND94: C95.1, J95.1, U95.2, U95.3, U95.4, U95.5, U95.8
GND95: C96.1, J96.1, U96.2, U96.3, U96.4, U96.5, U96.8
GND96: C97.1, J97.1, U97.2, U97.3, U97.4, U97.5, U97.8
GND97: C98.1, J98.1, U98.2, U98.3, U98.4, U98.5, U98.8
GND98: C99.1, J99.1, U99.2, U99.3, U99.4, U99.5, U99.8
GND99: C100.1, J100.1, U100.2, U100.3, U100.4, U100.5, U100.8
GND100: C101.1, J101.1, U101.2, U101.3, U101.4, U101.5, U101.8
GND101: C102.1, J102.1, U102.2, U102.3, U102.4, U102.5, U102.8
GND102: C103.1, J103.1, U103.2, U103.3, U103.4, U103.5, U103.8
GND103: C104.1, J104.1, U104.2, U104.3, U104.4, U104.5, U104.8
GND104: C105.1, J105.1, U105.2, U105.3, U105.4, U105.5, U105.8
GND105: C106.1, J106.1, U106.2, U106.3, U106.4, U106.5, U106.8
GND106: C107.1, J107.1, U107.2, U107.3, U107.4, U107.5, U107.8
GND107: C108.1, J108.1, U108.2, U108.3, U108.4, U108.5, U108.8
GND108: C109.1, J109.1, U109.2, U109.3, U109.4, U109.5, U109.8
GND109: C110.1, J110.1, U110.2, U110.3, U110.4, U110.5, U110.8
OUT+: J1.3, U1.7
OUT+1: J2.3, U2.7
OUT+2: J3.3, U3.7
OUT+3: J4.3, U4.7
OUT+4: J5.3, U5.7
OUT+5: J6.3, U6.7
OUT+6: J7.3, U7.7
OUT+7: J8.3, U8.7
OUT+8: J9.3, U9.7
OUT+9: J10.3, U10.7
OUT+10: J11.3, U11.7
OUT+11: J12.3, U12.7
OUT+12: J13.3, U13.7
OUT+13: J14.3, U14.7
OUT+14: J15.3, U15.7
OUT+15: J16.3, U16.7
OUT+16: J17.3, U17.7
OUT+17: J18.3, U18.7
OUT+18: J19.3, U19.7
OUT+19: J20.3, U20.7
OUT+20: J21.3, U21.7
OUT+21: J22.3, U22.7
OUT+22: J23.3, U23.7
OUT+23: J24.3, U24.7
OUT+24: J25.3, U25.7
OUT+25: J26.3, U26.7
OUT+26: J27.3, U27.7
OUT+27: J28.3, U28.7
OUT+28: J29.3, U29.7
OUT+29: J30.3, U30.7
OUT+30: J31.3, U31.7
OUT+31: J32.3, U32.7
OUT+32: J33.3, U33.7
OUT+33: J34.3, U34.7
OUT+34: J35.3, U35.7
OUT+35: J36.3, U36.7
OUT+36: J37.3, U37.7
OUT+37: J38.3, U38.7
OUT+38: J39.3, U39.7
OUT+39: J40.3, U40.7
OUT+40: J41.3, U41.7
OUT+41: J42.3, U42.7
OUT+42: J43.3, U43.7
OUT+43: J44.3, U44.7
OUT+44: J45.3, U45.7
OUT+45: J46.3, U46.7
OUT+46: J47.3, U47.7
OUT+47: J48.3, U48.7
OUT+48: J49.3, U49.7
OUT+49: J50.3, U50.7
OUT+50: J51.3, U51.7
OUT+51: J52.3, U52.7
OUT+52: J53.3, U53.7
OUT+53: J54.3, U54.7
OUT+54: J55.3, U55.7
OUT+55: J56.3, U56.7
OUT+56: J57.3, U57.7
OUT+57: J58.3, U58.7
OUT+58: J59.3, U59.7
OUT+59: J60.3, U60.7
OUT+60: J61.3, U61.7
OUT+61: J62.3, U62.7
OUT+62: J63.3, U63.7
OUT+63: J64.3, U64.7
OUT+64: J65.3, U65.7
OUT+65: J66.3, U66.7
OUT+66: J67.3, U67.7
OUT+67: J68.3, U68.7
OUT+68: J69.3, U69.7
OUT+69: J70.3, U70.7
OUT+70: J71.3, U71.7
OUT+71: J72.3, U72.7
OUT+72: J73.3, U73.7
OUT+73: J74.3, U74.7
OUT+74: J75.3, U75.7
OUT+75: J76.3, U76.7
OUT+76: J77.3, U77.7
OUT+77: J78.3, U78.7
OUT+78: J79.3, U79.7
OUT+79: J80.3, U80.7
OUT+80: J81.3, U81.7
OUT+81: J82.3, U82.7
OUT+82: J83.3, U83.7
OUT+83: J84.3, U84.7
OUT+84: J85.3, U85.7
OUT+85: J86.3, U86.7
OUT+86: J87.3, U87.7
OUT+87: J88.3, U88.7
OUT+88: J89.3, U89.7
OUT+89: J90.3, U90.7
OUT+90: J91.3, U91.7
OUT+91: J92.3, U92.7
OUT+92: J93.3, U93.7
OUT+93: J94.3, U94.7
OUT+94: J95.3, U95.7
OUT+95: J96.3, U96.7
OUT+96: J97.3, U97.7
OUT+97: J98.3, U98.7
OUT+98: J99.3, U99.7
OUT+99: J100.3, U100.7
OUT+100: J101.3, U101.7
OUT+101: J102.3, U102.7
OUT+102: J103.3, U103.7
OUT+103: J104.3, U104.7
OUT+104: J105.3, U105.7
OUT+105: J106.3, U106.7
OUT+106: J107.3, U107.7
OUT+107: J108.3, U108.7
OUT+108: J109.3, U109.7
OUT+109: J110.3, U110.7
OUT-: J1.4, U1.1
OUT-1: J2.4, U2.1
OUT-2: J3.4, U3.1
OUT-3: J4.4, U4.1
OUT-4: J5.4, U5.1
OUT-5: J6.4, U6.1
OUT-6: J7.4, U7.1
OUT-7: J8.4, U8.1
OUT-8: J9.4, U9.1
OUT-9: J10.4, U10.1
OUT-10: J11.4, U11.1
OUT-11: J12.4, U12.1
OUT-12: J13.4, U13.1
OUT-13: J14.4, U14.1
OUT-14: J15.4, U15.1
OUT-15: J16.4, U16.1
OUT-16: J17.4, U17.1
OUT-17: J18.4, U18.1
OUT-18: J19.4, U19.1
OUT-19: J20.4, U20.1
OUT-20: J21.4, U21.1
OUT-21: J22.4, U22.1
OUT-22: J23.4, U23.1
OUT-23: J24.4, U24.1
OUT-24: J25.4, U25.1
OUT-25: J26.4, U26.1
OUT-26: J27.4, U27.1
OUT-27: J28.4, U28.1
OUT-28: J29.4, U29.1
OUT-29: J30.4, U30.1
OUT-30: J31.4, U31.1
OUT-31: J32.4, U32.1
OUT-32: J33.4, U33.1
OUT-33: J34.4, U34.1
OUT-34: J35.4, U35.1
OUT-35: J36.4, U36.1
OUT-36: J37.4, U37.1
OUT-37: J38.4, U38.1
OUT-38: J39.4, U39.1
OUT-39: J40.4, U40.1
OUT-40: J41.4, U41.1
OUT-41: J42.4, U42.1
OUT-42: J43.4, U43.1
OUT-43: J44.4, U44.1
OUT-44: J45.4, U45.1
OUT-45: J46.4, U46.1
OUT-46: J47.4, U47.1
OUT-47: J48.4, U48.1
OUT-48: J49.4, U49.1
OUT-49: J50.4, U50.1
OUT-50: J51.4, U51.1
OUT-51: J52.4, U52.1
OUT-52: J53.4, U53.1
OUT-53: J54.4, U54.1
OUT-54: J55.4, U55.1
OUT-55: J56.4, U56.1
OUT-56: J57.4, U57.1
OUT-57: J58.4, U58.1
OUT-58: J59.4, U59.1
OUT-59: J60.4, U60.1
OUT-60: J61.4, U61.1
OUT-61: J62.4, U62.1
OUT-62: J63.4, U63.1
OUT-63: J64.4, U64.1
OUT-64: J65.4, U65.1
OUT-65: J66.4, U66.1
OUT-66: J67.4, U67.1
OUT-67: J68.4, U68.1
OUT-68: J69.4, U69.1
OUT-69: J70.4, U70.1
OUT-70: J71.4, U71.1
OUT-71: J72.4, U72.1
OUT-72: J73.4, U73.1
OUT-73: J74.4, U74.1
OUT-74: J75.4, U75.1
OUT-75: J76.4, U76.1
OUT-76: J77.4, U77.1
OUT-77: J78.4, U78.1
OUT-78: J79.4, U79.1
OUT-79: J80.4, U80.1
OUT-80: J81.4, U81.1
OUT-81: J82.4, U82.1
OUT-82: J83.4, U83.1
OUT-83: J84.4, U84.1
OUT-84: J85.4, U85.1
OUT-85: J86.4, U86.1
OUT-86: J87.4, U87.1
OUT-87: J88.4, U88.1
OUT-88: J89.4, U89.1
OUT-89: J90.4, U90.1
OUT-90: J91.4, U91.1
OUT-91: J92.4, U92.1
OUT-92: J93.4, U93.1
OUT-93: J94.4, U94.1
OUT-94: J95.4, U95.1
OUT-95: J96.4, U96.1
OUT-96: J97.4, U97.1
OUT-97: J98.4, U98.1
OUT-98: J99.4, U99.1
OUT-99: J100.4, U100.1
OUT-100: J101.4, U101.1
OUT-101: J102.4, U102.1
OUT-102: J103.4, U103.1
OUT-103: J104.4, U104.1
OUT-104: J105.4, U105.1
OUT-105: J106.4, U106.1
OUT-106: J107.4, U107.1
OUT-107: J108.4, U108.1
OUT-108: J109.4, U109.1
OUT-109: J110.4, U110.1
VCC: C4.2, J1.2, U1.6
VCC1: C1.2, J2.2, U2.6
VCC2: C2.2, J3.2, U3.6
VCC3: C3.2, J4.2, U4.6
VCC4: C5.2, J5.2, U5.6
VCC5: C6.2, J6.2, U6.6
VCC6: C7.2, J7.2, U7.6
VCC7: C8.2, J8.2, U8.6
VCC8: C9.2, J9.2, U9.6
VCC9: C10.2, J10.2, U10.6
VCC10: C11.2, J11.2, U11.6
VCC11: C12.2, J12.2, U12.6
VCC12: C13.2, J13.2, U13.6
VCC13: C14.2, J14.2, U14.6
VCC14: C15.2, J15.2, U15.6
VCC15: C16.2, J16.2, U16.6
VCC16: C17.2, J17.2, U17.6
VCC17: C18.2, J18.2, U18.6
VCC18: C19.2, J19.2, U19.6
VCC19: C20.2, J20.2, U20.6
VCC20: C21.2, J21.2, U21.6
VCC21: C22.2, J22.2, U22.6
VCC22: C23.2, J23.2, U23.6
VCC23: C24.2, J24.2, U24.6
VCC24: C25.2, J25.2, U25.6
VCC25: C26.2, J26.2, U26.6
VCC26: C27.2, J27.2, U27.6
VCC27: C28.2, J28.2, U28.6
VCC28: C29.2, J29.2, U29.6
VCC29: C30.2, J30.2, U30.6
VCC30: C31.2, J31.2, U31.6
VCC31: C32.2, J32.2, U32.6
VCC32: C33.2, J33.2, U33.6
VCC33: C34.2, J34.2, U34.6
VCC34: C35.2, J35.2, U35.6
VCC35: C36.2, J36.2, U36.6
VCC36: C37.2, J37.2, U37.6
VCC37: C38.2, J38.2, U38.6
VCC38: C39.2, J39.2, U39.6
VCC39: C40.2, J40.2, U40.6
VCC40: C41.2, J41.2, U41.6
VCC41: C42.2, J42.2, U42.6
VCC42: C43.2, J43.2, U43.6
VCC43: C44.2, J44.2, U44.6
VCC44: C45.2, J45.2, U45.6
VCC45: C46.2, J46.2, U46.6
VCC46: C47.2, J47.2, U47.6
VCC47: C48.2, J48.2, U48.6
VCC48: C49.2, J49.2, U49.6
VCC49: C50.2, J50.2, U50.6
VCC50: C51.2, J51.2, U51.6
VCC51: C52.2, J52.2, U52.6
VCC52: C53.2, J53.2, U53.6
VCC53: C54.2, J54.2, U54.6
VCC54: C55.2, J55.2, U55.6
VCC55: C56.2, J56.2, U56.6
VCC56: C57.2, J57.2, U57.6
VCC57: C58.2, J58.2, U58.6
VCC58: C59.2, J59.2, U59.6
VCC59: C60.2, J60.2, U60.6
VCC60: C61.2, J61.2, U61.6
VCC61: C62.2, J62.2, U62.6
VCC62: C63.2, J63.2, U63.6
VCC63: C64.2, J64.2, U64.6
VCC64: C65.2, J65.2, U65.6
VCC65: C66.2, J66.2, U66.6
VCC66: C67.2, J67.2, U67.6
VCC67: C68.2, J68.2, U68.6
VCC68: C69.2, J69.2, U69.6
VCC69: C70.2, J70.2, U70.6
VCC70: C71.2, J71.2, U71.6
VCC71: C72.2, J72.2, U72.6
VCC72: C73.2, J73.2, U73.6
VCC73: C74.2, J74.2, U74.6
VCC74: C75.2, J75.2, U75.6
VCC75: C76.2, J76.2, U76.6
VCC76: C77.2, J77.2, U77.6
VCC77: C78.2, J78.2, U78.6
VCC78: C79.2, J79.2, U79.6
VCC79: C80.2, J80.2, U80.6
VCC80: C81.2, J81.2, U81.6
VCC81: C82.2, J82.2, U82.6
VCC82: C83.2, J83.2, U83.6
VCC83: C84.2, J84.2, U84.6
VCC84: C85.2, J85.2, U85.6
VCC85: C86.2, J86.2, U86.6
VCC86: C87.2, J87.2, U87.6
VCC87: C88.2, J88.2, U88.6
VCC88: C89.2, J89.2, U89.6
VCC89: C90.2, J90.2, U90.6
VCC90: C91.2, J91.2, U91.6
VCC91: C92.2, J92.2, U92.6
VCC92: C93.2, J93.2, U93.6
VCC93: C94.2, J94.2, U94.6
VCC94: C95.2, J95.2, U95.6
VCC95: C96.2, J96.2, U96.6
VCC96: C97.2, J97.2, U97.6
VCC97: C98.2, J98.2, U98.6
VCC98: C99.2, J99.2, U99.6
VCC99: C100.2, J100.2, U100.6
VCC100: C101.2, J101.2, U101.6
VCC101: C102.2, J102.2, U102.6
VCC102: C103.2, J103.2, U103.6
VCC103: C104.2, J104.2, U104.6
VCC104: C105.2, J105.2, U105.6
VCC105: C106.2, J106.2, U106.6
VCC106: C107.2, J107.2, U107.6
VCC107: C108.2, J108.2, U108.6
VCC108: C109.2, J109.2, U109.6
VCC109: C110.2, J110.2, U110.6

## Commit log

2023-01-06 initial layout, ds, and readme almost done
2023-01-06 add prod_id to mic
2023-01-06 drc error approvals
2023-01-06 Center text in schematic frame
2023-01-06 production gerbers v10
2023-01-09 App note (Vesper AN7) about use case in smart speakers
2023-01-09 Updated datasheet
2023-02-01 Move Eagle Files into Hardware Folder

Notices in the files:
parts and their libraries:
SparkFun-Capacitors: Licensing: Creative Commons ShareAlike 4.0 International - https://creativecommons.org/licenses/by-sa/4.0
SparkFun-Aesthetics: Released under the Creative Commons Attribution Share-Alike 4.0 License
SparkFun-Aesthetics: https://creativecommons.org/licenses/by-sa/4.0
